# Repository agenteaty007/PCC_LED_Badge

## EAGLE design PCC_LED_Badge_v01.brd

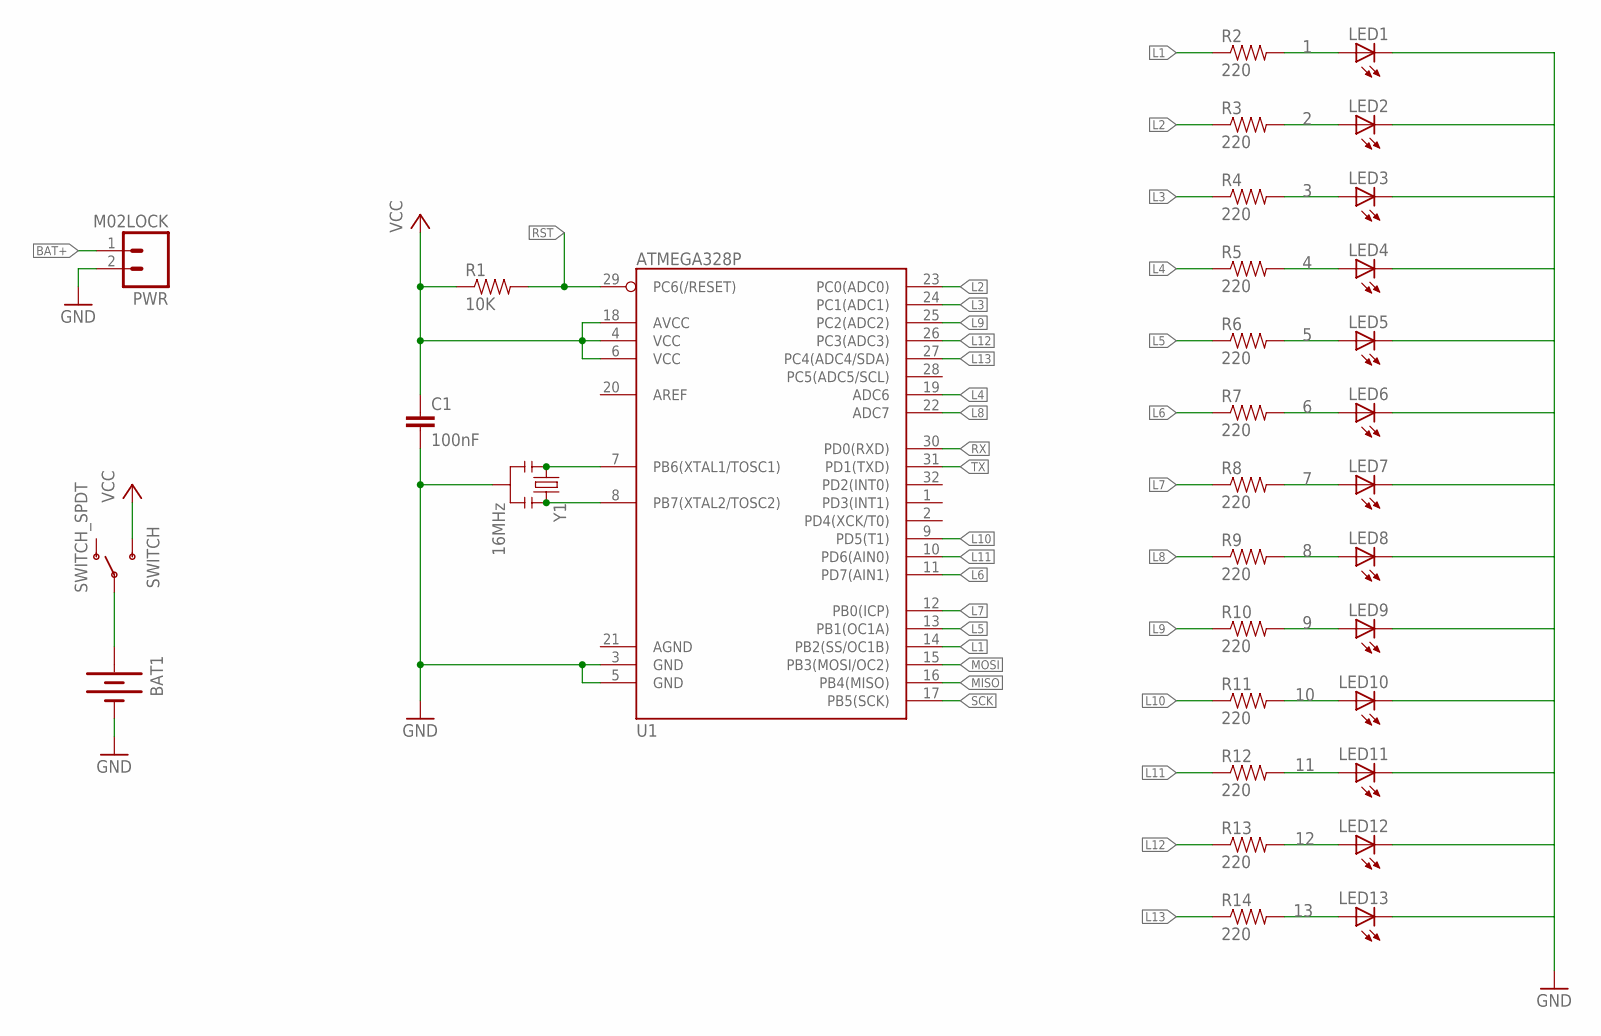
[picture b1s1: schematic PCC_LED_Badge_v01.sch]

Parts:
BAT1: BATTERY20SMD; BATTCON_20MM
C1: 100nF; 0603-CAP
LED1, LED2, LED3, LED4, LED5, LED6, LED7, LED8, LED9, LED10, LED11, LED12, LED13: LED0603; LED-0603
PWR: M02LOCK; 1X02_LOCK
R1: 10K; 0603-RES
R2, R3, R4, R5, R6, R7, R8, R9, R10, R11, R12, R13, R14: 220; 0603-RES
SWITCH: SWITCH_SPDT; KPS-1290
U1: ATMEGA328P; TQFP32-08
Y1: 16MHz; RESONATOR-SMD

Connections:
1: LED1.A, R2.2
2: LED2.A, R3.2
3: LED3.A, R4.2
4: LED4.A, R5.2
5: LED5.A, R6.2
6: LED6.A, R7.2
7: LED7.A, R8.2
8: LED8.A, R9.2
9: LED9.A, R10.2
10: LED10.A, R11.2
11: LED11.A, R12.2
12: LED12.A, R13.2
13: LED13.A, R14.2
BAT+: BAT1.1 (+), PWR.1, SWITCH.P
GND: BAT1.2 (-), C1.2, LED1.C, LED2.C, LED3.C, LED4.C, LED5.C, LED6.C, LED7.C, LED8.C, LED9.C, LED10.C, LED11.C, LED12.C, LED13.C, PWR.2, U1.3 (GND), U1.5 (GND), Y1.2
L1: R2.1, U1.14 (PB2(SS/OC1B))
L2: R3.1, U1.23 (PC0(ADC0))
L3: R4.1, U1.24 (PC1(ADC1))
L4: R5.1, U1.19 (ADC6)
L5: R6.1, U1.13 (PB1(OC1A))
L6: R7.1, U1.11 (PD7(AIN1))
L7: R8.1, U1.12 (PB0(ICP))
L8: R9.1, U1.22 (ADC7)
L9: R10.1, U1.25 (PC2(ADC2))
L10: R11.1, U1.9 (PD5(T1))
L11: R12.1, U1.10 (PD6(AIN0))
L12: R13.1, U1.26 (PC3(ADC3))
L13: R14.1, U1.27 (PC4(ADC4/SDA))
MISO: U1.16 (PB4(MISO))
MOSI: U1.15 (PB3(MOSI/OC2))
unnamed: U1.7 (PB6(XTAL1/TOSC1)), Y1.1
unnamed: U1.8 (PB7(XTAL2/TOSC2)), Y1.3
RST: R1.2, U1.29 (PC6(/RESET))
RX: U1.30 (PD0(RXD))
SCK: U1.17 (PB5(SCK))
TX: U1.31 (PD1(TXD))
VCC: C1.1, R1.1, SWITCH.S, U1.4 (VCC), U1.6 (VCC), U1.18 (AVCC)

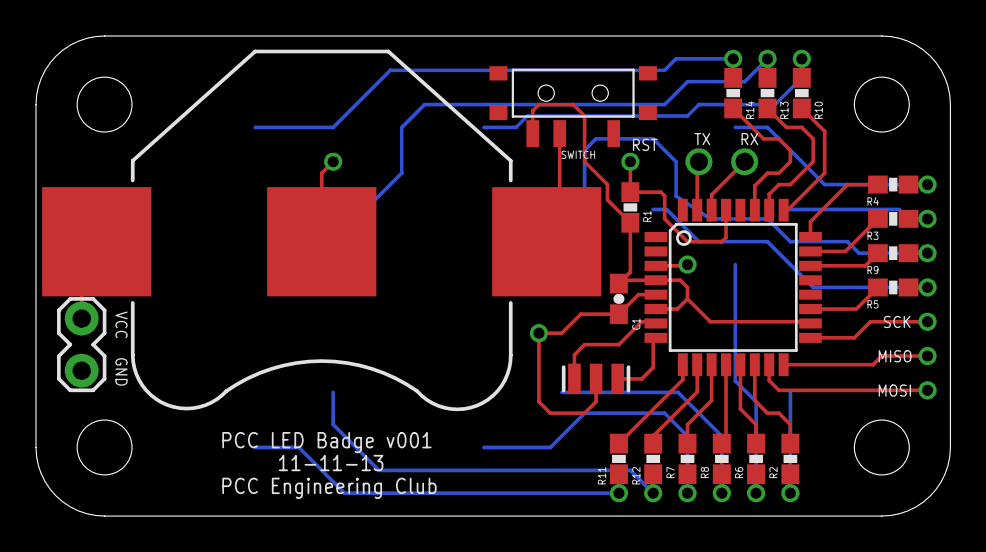
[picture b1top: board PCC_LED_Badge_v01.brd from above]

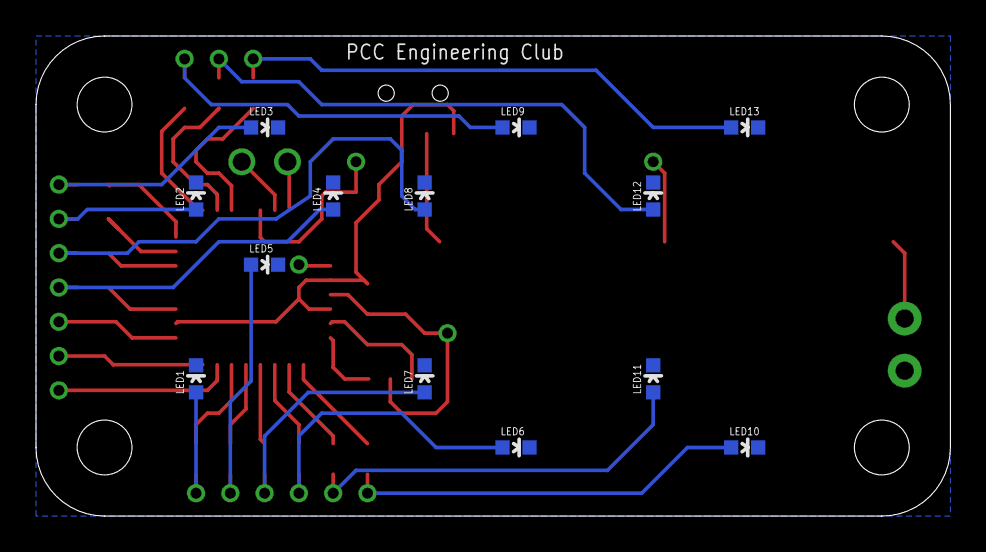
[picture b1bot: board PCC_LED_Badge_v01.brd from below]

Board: 2 copper layers, 50.8 x 26.7 mm, 37 parts (13 on the bottom side), 32 nets.

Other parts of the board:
U$2, U$3, U$4, U$5: STAND-OFF-TIGHT

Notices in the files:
parts and their libraries:
SparkFun-DigitalIC: Licensing: CC v3.0 Share-Alike You are welcome to use this library for commercial purposes.
